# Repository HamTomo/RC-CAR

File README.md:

# RC-CAR

RC Car Notes

------------------------------------------------------------
WIP:
-----
- Laptop driven TX
	+ Schematic
	+ Layout
- What is sent per TX switch?
	+
- Figure out why not pairing
	+ 

------------------------------------------------------------
To Do:
-----
- Identify TX/RX IC
- How does TX/RX pair?
- What is sent per TX switch?
	+ Confirm binary on/off at RX
- Layout PCBA
- ID repurpose points
- Laptop driven TX
	+ Mockup
- Measure Motor Series Resistance
- Measure components
- Platform characteristics
	- Acceleration
	- Turning Radius
	- Steering Motor Torque/Load Curves
	- Drive Motor Torque/Load Curves

------------------------------------------------------------

------------------------------------------------------------
Done:
-----
- Schematic Drawn
- EBoM First Pass
- Translate Motor Driver IC

------------------------------------------------------------

Inspectrum analysis

Signal 1
First instance start:		1.747s
Last instance start:		9.0616s
Time between instances:	25.36ms (Assume 25ms?)
No. of instances:			289
No. per press:			58

Instance Breakdown
2 blocks
1st 868ms
2nd 864ms
SS 2.108
3 symbols per block?
011

Signal 2
First instance start:		10.081s
Last instance start:		15.1627s
Time between instances:	25.392 

Instance Breakdown
2 blocks
1st 880us
2nd 880us
SS 2.01ms
3 symbols per block?
011

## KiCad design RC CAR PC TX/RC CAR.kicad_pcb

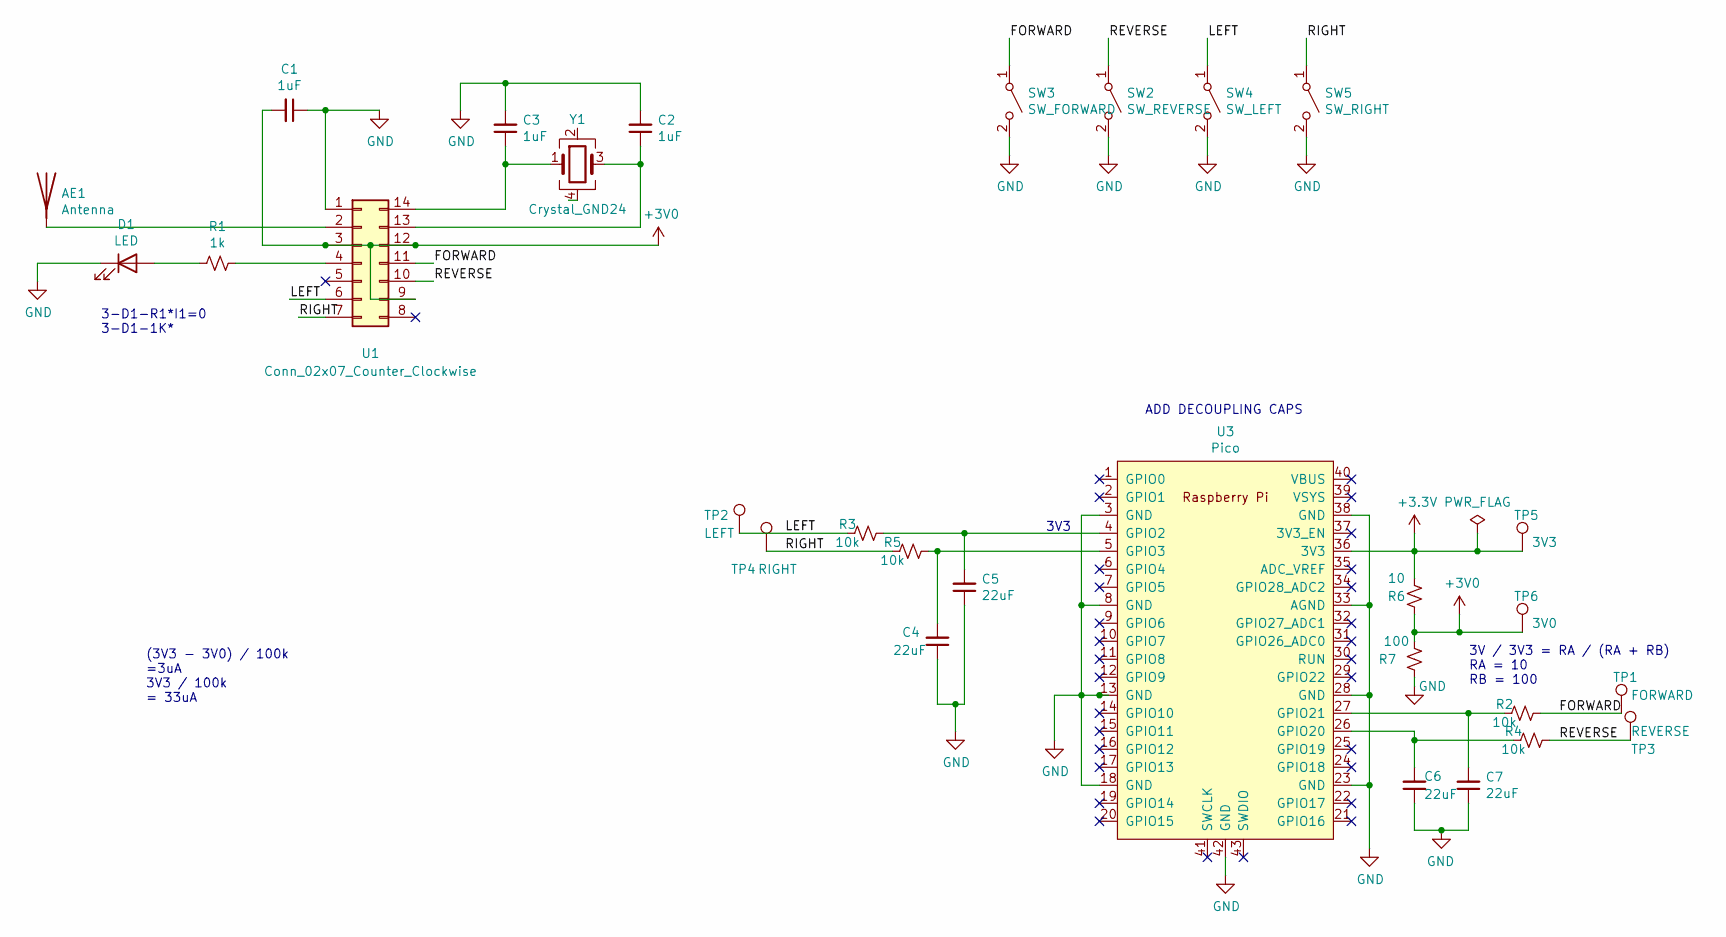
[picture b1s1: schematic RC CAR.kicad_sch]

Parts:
AE1: Antenna; SZJJX_CAR_TX_2.4GHz_Left
C1, C2, C3: 1uF; C_0603_1608Metric
C4, C5, C6, C7: 22uF; C_0603_1608Metric
D1: LED; DS144_Luxeon_LED_SMD_1CAT
R1: 1k; R_0603_1608Metric
R2, R3, R4, R5: 10k; R_0603_1608Metric
R6: 10; R_0603_1608Metric
R7: 100; R_0603_1608Metric
SW2: SW_REVERSE; RC TLS TacSwitch
SW3: SW_FORWARD; RC TLS TacSwitch
SW4: SW_LEFT; RC TLS TacSwitch
SW5: SW_RIGHT; RC TLS TacSwitch
TP1: FORWARD; Test_Point_0805_2012Metric
TP2: LEFT; Test_Point_0805_2012Metric
TP3: REVERSE; Test_Point_0805_2012Metric
TP4: RIGHT; Test_Point_0805_2012Metric
TP5: 3V3; Test_Point_0805_2012Metric
TP6: 3V0; Test_Point_0805_2012Metric
U1: Conn_02x07_Counter_Clockwise; SOIC-14_3.9x8.7mm_P1.27mm
U3: Pico; Pico_Pi_Connector
Y1: Crystal_GND24; Crystal_SMD_SeikoEpson_FA238V-4Pin_3.2x2.5mm

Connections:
+3V0: C1.2, R6.1, R7.2, TP6.1, U1.3, U1.9, U1.12
+3V3: R6.2, TP5.1, U3.36 (3V3)
/FORWARD: R2.1, SW3.1 (A), TP1.1, U1.11
/LEFT: R3.2, SW4.1 (A), TP2.1, U1.6
/REVERSE: R4.1, SW2.1 (A), TP3.1, U1.10
/RIGHT: R5.2, SW5.1 (A), TP4.1, U1.7
GND: C1.1, C2.2, C3.2, C4.1, C5.1, C6.1, C7.1, D1.1 (K), R7.1, SW2.2 (B), SW3.2 (B), SW4.2 (B), SW5.2 (B), U1.1, U3.3 (GND), U3.8 (GND), U3.13 (GND), U3.18 (GND), U3.23 (GND), U3.28 (GND), U3.33 (AGND), U3.38 (GND), U3.42 (GND)
unnamed: AE1.1 (A), U1.2
unnamed: C2.1, U1.13, Y1.3
unnamed: C3.1, U1.14, Y1.1
unnamed: C4.2, R5.1, U3.5 (GPIO3)
unnamed: C5.2, R3.1, U3.4 (GPIO2)
unnamed: D1.2 (A), R1.2
unnamed: R1.1, U1.4
unnamed: C6.2, R4.2, U3.26 (GPIO20)
unnamed: C7.2, R2.2, U3.27 (GPIO21)

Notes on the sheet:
3V / 3V3 = RA / (RA + RB) RA = 10 RB = 100
3V3
ADD DECOUPLING CAPS
(3V3 - 3V0) / 100k =3uA 3V3 / 100k = 33uA
3-D1-R1*I1=0 3-D1-1K*

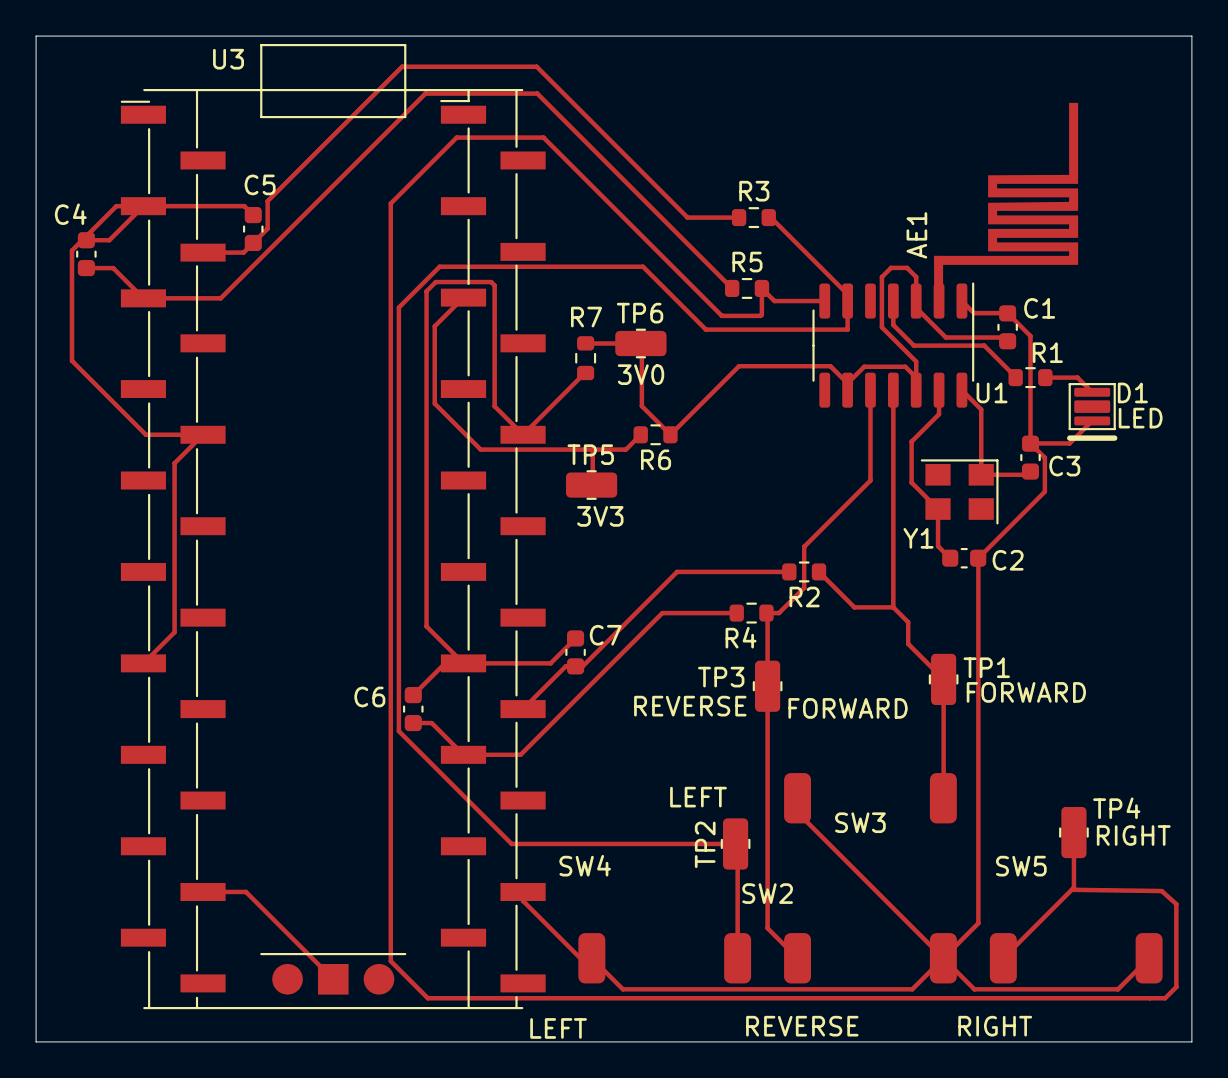
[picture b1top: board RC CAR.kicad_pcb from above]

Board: 2 copper layers, 64.2 x 55.9 mm, 29 parts (0 on the bottom side), 16 nets.

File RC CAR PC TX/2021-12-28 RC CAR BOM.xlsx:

Source: | /Users/hamish/Library/Mobile Documents/com~apple~CloudDocs/Projects/Active/RC-C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
Date: | Tuesday, 28 December 2021 at 15:26:19
Tool: | Eeschema (6.0.0-0)
Generator: | /Applications/KiCad/KiCad.app/Contents/SharedSupport/plugins/bom_csv_grouped_by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
Component Count: | 29
Ref | Qnty | Value | Cmp name | Footprint | Description | Vendor | Part identified | Footprint | Datasheet
AE1, | 1 | Antenna | Antenna | RF_Antenna:SZJJX_CAR_TX_2.4GHz_Left | Antenna |  | Yes | TBC | No
C1, C2, C3, | 3 | 1uF | C_Small | Capacitor_SMD:C_0603_1608Metric | Unpolarized capacitor, small symbol |  | Yes | Yes | Yes
C4, C5, C6, C7, | 4 | 22uF | C_Small | Capacitor_SMD:C_0603_1608Metric | Unpolarized capacitor, small symbol |  | Yes | Yes | Yes
D1, | 1 | LED | LED |  | Light emitting diode |  | Yes | TBC | Yes
R1, | 1 | 1k | R_Small_US | Resistor_SMD:R_0603_1608Metric | Resistor, small US symbol |  | Yes | Yes | Yes
R2, R3, R4, R5, | 4 | 10k | R_Small_US | Resistor_SMD:R_0603_1608Metric | Resistor, small US symbol |  | Yes | Yes | Yes
R6, | 1 | 10 | R_Small_US | Resistor_SMD:R_0603_1608Metric | Resistor, small US symbol |  | Yes | Yes | Yes
R7, | 1 | 100 | R_Small_US | Resistor_SMD:R_0603_1608Metric | Resistor, small US symbol |  | Yes | Yes | Yes
SW2, SW3, SW4, SW5, | 4 | SW_SPST | SW_SPST |  | Single Pole Single Throw (SPST) switch |  | Yes | Yes | Yes
TP1, | 1 | FORWARD | TestPoint | TestPoint:Test_Point_0805_2012Metric | test point |  | Yes | Yes | Yes
TP2, | 1 | LEFT | TestPoint | TestPoint:Test_Point_0805_2012Metric | test point |  | Yes | Yes | Yes
TP3, | 1 | REVERSE | TestPoint | TestPoint:Test_Point_0805_2012Metric | test point |  | Yes | Yes | Yes
TP4, | 1 | RIGHT | TestPoint | TestPoint:Test_Point_0805_2012Metric | test point |  | Yes | Yes | Yes
TP5, | 1 | 3V3 | TestPoint | TestPoint:Test_Point_0805_2012Metric | test point |  | Yes | Yes | Yes
TP6, | 1 | 3V0 | TestPoint | TestPoint:Test_Point_0805_2012Metric | test point |  | Yes | Yes | Yes
U1, | 1 | Conn_02x07_Counter_Clockwise | Conn_02x07_Counter_Clockwise | Package_SO:SOIC-14_3.9x8.7mm_P1.27mm | TX SOIC |  | Yes | Yes | No
U3, | 1 | Pico | Pico-MCU_RaspberryPi_and_Boards |  |  |  | Yes | TBC | Yes
Y1, | 1 | Crystal | Crystal | 4-SMD No Lead |  |  | Yes | Yes | Yes

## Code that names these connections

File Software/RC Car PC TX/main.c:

/******************************************
*	
* 	main.c for RC-CAR PC TX
* 
* 	Version:	1.0
* 	Date:		2022-05-22
* 	Author:		Hamish T
* 
*	Enable GPIO on pins
*	GP0, GP1, GP2, GP3
*	Output, Default set high
*	
*	REVERSE	SW2		GPIO2
* 	FORWARD	SW3		GPIO3
* 	LEFT	SW4		GPIO20
* 	RIGHT	SW5		GPIO21
*
*
*******************************************/

#include <stdio.h>
#include "pico/stdlib.h"
#include "hardware/gpio.h"
#include "pico/binary_info.h"
//Full relative address /../pico-sdk/src/common/pico_stdlib/include/pico/stdlib.h

const uint LED_PIN = 25;
const uint REVERSE = 20;
const uint FORWARD = 21;
const uint LEFT = 2;
const uint RIGHT = 3;

void test_drive(void)
{
	/*Cycle through each direction*/
	//FORWARD
	puts("FORWARD\n");
	gpio_put(FORWARD, 0);
	sleep_ms(250);
	gpio_put(FORWARD, 1);
	sleep_ms(1000);

	//REVERSE
	puts("REVERSE\n");
	gpio_put(REVERSE, 0);
	sleep_ms(250);
	gpio_put(REVERSE, 1);
	sleep_ms(1000);

	//LEFT
	puts("LEFT\n");
	gpio_put(LEFT, 0);
	sleep_ms(250);
	gpio_put(LEFT, 1);
	sleep_ms(1000);

	//RIGHT
	puts("RIGHT\n");
	gpio_put(RIGHT, 0);
	sleep_ms(250);
	gpio_put(RIGHT, 1);
	sleep_ms(1000);
}

void gpio_init_all(void)
{
	stdio_init_all();

	gpio_init (LED_PIN);
	gpio_init (FORWARD);
	gpio_init (REVERSE);
	gpio_init (LEFT);
	gpio_init (RIGHT);

	//set outputs
  	gpio_set_dir(LED_PIN, GPIO_OUT);
	gpio_set_dir(FORWARD, GPIO_OUT);
	gpio_set_dir(REVERSE, GPIO_OUT);
	gpio_set_dir(RIGHT, GPIO_OUT);
	gpio_set_dir(LEFT, GPIO_OUT);

	//Set starting output direction
	gpio_put(FORWARD, 1);
	gpio_put(REVERSE, 1);
	gpio_put(LEFT, 1);
	gpio_put(RIGHT, 1);
	gpio_put(LED_PIN, 1);

}



int main()
{
   bi_decl(bi_program_description("This is a RC Car test binary."));
   bi_decl(bi_1pin_with_name(LED_PIN, "On-board LED"));

   gpio_init_all();  



   while (true)
   {
   		gpio_put(LED_PIN, 1);
		sleep_ms(250);
		gpio_put(LED_PIN, 0);
		sleep_ms(250);
		puts("Blink Blink\n");
		gpio_put(LED_PIN, 1);
		sleep_ms(250);
		gpio_put(LED_PIN, 0);
		sleep_ms(250);

		test_drive();
		sleep_ms(1000);

	}
}

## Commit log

2021-12-18 Files commit
2021-12-18 update gitignore
2021-12-18 Add large files
2021-12-19 Combine files
2022-02-06 Updated PCB layout for PCBA 2.0
2022-02-13 Updated files
2022-05-22 Test script that cycles through controller switches and outputs direction to serial
